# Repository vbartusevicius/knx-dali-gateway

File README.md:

# KNX–DALI Gateway

Open-source DIN-rail gateway between a wired **KNX TP** line and one **DALI / DALI-2** line: up to 64 control gear plus DALI-2 multi-master input devices, commissioned entirely through **ETS**. An optional integrated, isolated DALI bus supply runs from 20–32 V auxiliary DC (a 24 V PSU or the KNX white/yellow pair); the same input also powers the gateway core, with the KNX bus as a seamless fallback. The WiFi dashboard and MQTT are extras: lighting control and ETS provisioning never depend on them.

> [!NOTE]
> **Pre-hardware prototype.** Verified by native unit tests, a Docker KNX/DALI integration lab, KiCad DRC and isolation checks, JLCPCB footprint and pinout checks, and exact-solid CadQuery fit tests. No board has been powered on yet, and no KNX or DALI certification is claimed.

<p align="center">
  <a href="#downloads">Downloads</a> ·
  <a href="#screenshots">Screenshots</a> ·
  <a href="#hardware">Hardware</a> ·
  <a href="#building-one">Building one</a> ·
  <a href="#how-it-works">How it works</a> ·
  <a href="#development">Development</a>
</p>

---

## Downloads

| What | Where | Use |
| --- | --- | --- |
| **First install (USB)** | [`firmware-full-usb.bin`](https://github.com/vbartusevicius/knx-dali-gateway/releases/latest) | Bootloader, partition table and firmware in one image for an empty ESP32-C6. Connect the XIAO over USB-C and write it at `0x0`: `esptool.py --chip esp32c6 write_flash 0x0 firmware-full-usb.bin`. Clears all settings. |
| **Update** | [`firmware.bin`](https://github.com/vbartusevicius/knx-dali-gateway/releases/latest) | Drop it onto the **Firmware** tab of the web interface. Updates firmware and web UI together; settings are kept. |
| **ETS product database** | [`KnxDaliGateway.knxprod`](https://github.com/vbartusevicius/knx-dali-gateway/releases/latest) | Import into ETS 5.7 / 6: 64 lamp channels (DT6/DT7/DT8), 16 groups, broadcast, 8 DALI-2 input devices with up to 4 instances each (1,321 group objects). |
| **Hardware bundles** | [`knx-dali-gateway-hardware-v2.zip` / `v3.zip`](https://github.com/vbartusevicius/knx-dali-gateway/releases/latest) | Gerbers, JLCPCB BOM/CPL, STEP assemblies, printable STL/3MF case, `assembly_parts.csv`. |

---

## Screenshots

The web interface is built into the firmware and served by the ESP32-C6 itself (live WebSocket updates, no cloud):

<details>
<summary><b>More of the web interface</b>: lamp settings, groups and scenes, error log, bus monitor, settings</summary>

<br>

| Lamp settings | Groups & scenes |
| :---: | :---: |
|  |  |
| Device type, dimming curve, limits, fade, D4i or calculated power, ballast replacement | 16 scenes, 16 groups (G00–G15), group colour, membership written to the ballast |
| **Error log** | **Live DALI bus monitor** |
|  |  |
| Persistent NVS history with remedies | 8/16/24-bit frames and collisions: 1,024 rows on the device, 10,000 in the browser |
| **Settings** | |
|  | |
| WiFi, MQTT with Home Assistant auto-discovery, power model | |

- **Overview:** live level, DT8 colour (Tc, RGBW, xy), per-lamp power (native D4i Part 252 or calculated), lamp finder, fault codes; a second grid for DALI-2 buttons and sensors (IEC 62386-103 / 301–304).
- **Home Assistant:** one gateway device (total power and energy) plus every populated lamp with on/off, dimming, colour, power and fault entities.

</details>

<details>
<summary><b>Front-panel OLED pages</b>: V3 portrait 64×128, V2 landscape 128×64</summary>

<br>

The left button (SCROLL, plain bump) steps through the pages; holding it for 5 s starts the WiFi setup portal. The right button (RESET, bump with an X) reboots on a tap and toggles KNX programming mode when held for 5 s; both held for 10 s is a factory reset.

</details>

---

## Hardware

Two variants share the circuit blocks (`hardware/circuits/blocks/`), the XIAO ESP32-C6 pinout (`gateway/src/firmware/Board.hpp`) and the firmware:

| | **V3** (`v3`) | **V2** (`v2`) |
| --- | --- | --- |
| Width | 1 DIN (18 mm) | 2 DIN (36 mm) |
| Boards | 2: two-sided vertical `main`, front `ui` | 3: `main`, `interface`, `ui` |
| AUX core converter | TRACO TMR 2411 (2 W), on a tongue of `main` in the front protrusion | TRACO TRN 3-2411 (3 W), on the back of `main` |
| DALI terminal | WAGO 2086 push-in (SMD, hand-soldered), buttons beside the wire entries | MX126 screw |
| KNX / AUX | PST 1,0 pin strips (red/black, yellow/white plugs) | PST 1,0 KNX, MX126 screw AUX |
| Display | 0.96" 64×128 portrait SSD1312, solder flex tail | 0.96" 128×64 SSD1306 module, 4-pin header |
| Buttons | Omron B3U pressed through C-shaped spring tabs in the cover | same |
| Main ↔ UI link | 8-pin 0.5 mm FFC (Type B, 50 mm) | 10-pin JST-SH cable |
| Case | Side-opening clamshell, snap-fit | Two 2.5×10 screws, UI snaps |
| Release | [`hardware/releases/v3/`](hardware/releases/v3/README.md) | [`hardware/releases/v2/`](hardware/releases/v2/README.md) |

<details>
<summary><b>V3 renders</b>: assembly and boards</summary>

<br>

PCB artwork: [`main` top](hardware/releases/v3/main/renders/top.svg) · [bottom](hardware/releases/v3/main/renders/bottom.svg) · [`ui` top](hardware/releases/v3/ui/renders/top.svg) · [bottom](hardware/releases/v3/ui/renders/bottom.svg).
Fit drawings: [front](hardware/releases/v3/enclosure/fit_front.svg) · [side](hardware/releases/v3/enclosure/fit_side.svg).

</details>

<details>
<summary><b>V2 renders</b>: assembly and boards</summary>

<br>

PCB artwork: [`main` top](hardware/releases/v2/main/renders/top.svg) · [bottom](hardware/releases/v2/main/renders/bottom.svg) · [`interface` top](hardware/releases/v2/interface/renders/top.svg) · [bottom](hardware/releases/v2/interface/renders/bottom.svg) · [`ui` top](hardware/releases/v2/ui/renders/top.svg) · [bottom](hardware/releases/v2/ui/renders/bottom.svg).
Fit drawings: [front](hardware/releases/v2/enclosure/fit_front.svg) · [side](hardware/releases/v2/enclosure/fit_side.svg).

</details>

Pin table, LED chain and button ladder: [`hardware/docs/variants.md`](hardware/docs/variants.md). Pre-manufacturing reviews: [`review-2026-10-23.md`](hardware/docs/review-2026-10-23.md), [`review-2026-10-22.md`](hardware/docs/review-2026-10-22.md); rework for boards made from `59eea1f`: [`rework-rev-c.md`](hardware/docs/rework-rev-c.md).

---

## Building one

Each `hardware/releases/<variant>/` folder is a complete manufacturing package.

1. **PCBs with SMT assembly (JLCPCB).** Upload `panel/panel_gerbers.zip` (V3: 66.0 × 78.1 mm, 4 layers, 1.2 mm; V2: 98.5 × 76.6 mm, 4 layers, 1.6 mm) with **assembly on both sides**, `panel/panel_bom_jlc.csv` and `panel/panel_cpl_jlc.csv`. You order one PCB and one PCBA job and snap the boards apart. Per-board files are in `main/`, `ui/` (and `interface/` on V2). Compare `renders/top.svg` / `bottom.svg` with JLCPCB's placement preview.
   **Building it yourself:** `order_lcsc.csv` (LCSC BOM tool: map *LCSC Part Number* and *Quantity*) and `order_elsewhere.csv` (electronics LCSC does not sell, with Mouser / Digi-Key / TME numbers) cover every electronic part of one gateway; screws, foam and printed parts are only in `assembly_parts.csv`.
   **Other board houses** (Aisler, PCBWay, Eurocircuits, ...): every folder also has `<board>_odb.zip` (ODB++), Gerbers with drills and an IPC-D-356 netlist in `<board>_gerbers.zip`, and a generic `<board>_bom.csv` / `<board>_cpl.csv` with manufacturer part numbers and KiCad rotations.
2. **Hand-fitted parts.** `assembly_parts.csv` lists everything JLCPCB does not place (Kind `electronics`, `utility` or `printed`), with Mouser, Digi-Key and TME numbers:
   - the XIAO ESP32-C6 (pre-soldered) and its sockets;
   - the RECOM REC3-2415SRW/H2/A/CTRL DALI supply converter;
   - the TRACO AUX core converter;
   - Phoenix PST pin strips and plugs;
   - the OLED, the main-to-UI cable, and two jumper caps for `JP1`.
3. **Case.** Print `enclosure/base.stl` and one cover in PETG or ASA at 0.2 mm layers: `cover.stl`; V2 also has `cover_embossed.stl` (0.6 mm recessed legend). V3 has no front text: the button bumps tell the buttons apart.

<details>
<summary><b>V3 assembly order</b></summary>

1. Lay the OLED face down in the cover recess, fold its flex tail through the UI board's top notch and solder it to `J2`, put the 4 mm foam pad on the UI board, snap the UI board in.
2. Slide `main` into the base from the open left side, so the KNX/AUX pins pass into the right-side pockets and `J3` seats in the top opening.
3. Plug the FFC into `main J4` and `ui J1`, then close the cover over the left side and front until the four side snaps lock.

</details>

---

## How it works

- **KNX side:** an onsemi NCN5130 transceiver (TP1, 9-bit UART) charges a 470 µF store. An SCT2400 buck makes 5 V from it, with an undervoltage lockout above the NCN5130 reset level.
- **Core supply:** the AUX input feeds an isolated TRACO converter (SELV-AUX to SELV-KNX). A leaded priority path prefers it (TLV803 supervisor, 2N7002 and AO3401A switch) and a B5819W Schottky falls back to the KNX buck without a gap. A TI LM66100 keeps USB service power out of the core rail.
- **DALI supply:** the AUX input (PTC, TVS, reverse diode) feeds a RECOM REC3-2415SRW/H2/A/CTRL (24 V → 15 V, functional isolation), then a linear current limiter. The firmware can switch it off through an optocoupler on its `CTRL` pin, and jumper `JP1` disconnects it for an external DALI PSU.
- **DALI transceiver:** TX uses a MOSFET sink with bootstrap gate drive and a 275–350 mA fault clamp. RX uses a zener threshold with a constant-current detector. Both cross a 5.5 mm (reinforced, IEC 60664-1 230 V OVC III) milled barrier through TLP383 optocouplers.
- **Front panel:** the OLED (I2C), two buttons on one ADC ladder, and three WS2812B-MINI-V3J RGB LEDs with gull-wing legs (status, KNX, DALI) behind a 5 V level shifter. All passives are 0805 or larger except three 0603 bus caps next to the NCN5130 on V3; the NCN5130 (QFN-40) is the only leadless chip, as no leaded KNX transceiver exists.

---

## Development

| Folder | Contents |
| --- | --- |
| `gateway/` | ESP32-C6 firmware (C++17, ESP-IDF / PlatformIO) and native unit tests |
| `knxprod/` | ETS product database source and `.knxprod` builder |
| `simulation/` | DALI bus simulator and Docker KNX/DALI integration lab |
| `hardware/` | SKiDL circuits, KiCad layouts, part data, build scripts, release packages |
| `mechanical/` | CadQuery enclosures, fit drawings, front legends, 3D renders |

| Task | Command |
| --- | --- |
| Build, route, render, release and test both hardware variants | `python3 hardware/scripts/build.py` |
| One variant or step | `python3 hardware/scripts/build.py v3 --eda` (`--cad`, `--release`, `--test`) |
| Refresh the README images (after a release) | `docker compose --profile hardware run --rm -T cad "python3 mechanical/scripts/readme_images.py"` |
| Firmware tests and ESP32-C6 build (writes `firmware.bin` and `firmware-full-usb.bin`) | `pio test -d gateway -e native && pio run -d gateway -e dev_c6 -e release_c6` |
| Refresh the clangd compilation database | `pio run -d gateway -e dev_c6 -t compiledb` |
| Integration lab | `simulation/run-tests.sh` |
| ETS package | `ETS_CV_DIR=knxprod/ETS knxprod/scripts/package.sh` |
| Lint (Python, YAML, C++) | `docker compose --profile lint run --rm lint check .` |

Licences per folder: [`LICENSE.md`](LICENSE.md). Engineering rules and architecture notes: [`AGENTS.md`](AGENTS.md).

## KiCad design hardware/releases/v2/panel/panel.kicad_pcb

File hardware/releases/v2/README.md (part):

# KNX-DALI gateway hardware v2 (2 DIN, three boards)

**Revision C (2026-10-22).** Changes against rev B (`59eea1f`): AUX-powered core (TRACO TMR 1-2411 U9 on the back of main, hand-fitted, plus TI TPS2121 U10 priority mux with the KNX buck as fallback; U4 and C4 moved); XIAO LM66100 U7 (UI) CE on VOUT (no USB back-feed); DALI TX clamp 2R, gate divider 4k7/10k, RX pull-up 4k7 (interface), buck EN 100k (main); cover screw tab centred between the terminals and lips notched at the terminal bodies. Rev B boards and prints: follow [`hardware/docs/rework-rev-c.md`](../../docs/rework-rev-c.md).

**Hand-assembly revision (2026-11-11).** Every part is chosen for soldering with an iron:
- **Passives:** all 0805 or larger. The one exception is v3's three NCN5130 bus caps (C1 47 nF, C2 100 nF, C3 220 nF), which are 0603 so the chip's left side stays routable.
- **LEDs:** WS2812B-MINI-V3J with gull-wing legs (LCSC C22371519).
- **Crystal:** 2-pad 5032.
- **Core power path:** leaded parts (TLV803M U10, 2N7002 Q10, AO3401A Q9, B5819W D11) replace the VQFN TPS2121.
- **Still fine-pitch:** the NCN5130 (QFN-40; no leaded KNX transceiver exists: hot plate or hot air) and the LM66100 (SC-70-6, leaded).
- **Isolation:** DALI isolation is 5.5 mm (reinforced, IEC 60664-1 230 V OVC III PD2); SELV-AUX to SELV-KNX is 1 mm (functional).
- **Buttons:** left = SCROLL (plain bump), right = RESET (X bump).
- `<board>/<board>_assembly.pdf`: hand-soldering guide. One page per populated side (the bottom mirrored, as seen from below), each part's body, reference and value, a red dot on pin 1, a black corner on hand-fitted parts and one colour per value. Large parts are dashed under the small ones. A values page lists quantity, side and references.

Generated by `HARDWARE_VARIANT=v2 python3 hardware/scripts/release.py` from
`hardware/layout/v2/`, with the gates of every release: KiCad DRC 0 errors and 0
unrouted, every part orderable or hand-fit, every JLC part checked against
JLCPCB's part record, live stock and its EasyEDA footprint (pin for pin; the
placement file carries the fitted rotations and centres). CI
(`HARDWARE_VARIANT=v2`, `test_release_current.py`) fails as soon as the boards
no longer match this release.

| Board | Size | Layers | Position in the case | Folder |
|---|---|---|---|---|
| Main | 31.5 x 76.5 mm | 4 | flat in the base: KNX, 5 V, isolated DALI supply, all terminals | `main/` |
| Interface | 31.5 x 27.5 mm | 4 | plugged onto main (11 mm above it): isolated DALI TX/RX | `interface/` |
| UI | 31.5 x 40.5 mm | 4 | snapped into the cover: XIAO ESP32-C6, OLED, 2 buttons, 3 RGB LEDs | `ui/` |

The interface board has no case retention of its own: its two male headers
(J1 logic, J2 DALI, on its back) plug into main J6/J5 (8.5 mm sockets +
2.5 mm header plastic = 11.0 mm). DALI TX/RX reach it from the XIAO through
the main-to-UI cable (pins 7/8) and main J6. The only cable is that 10-pin
JST-SH jumper.

## Ordering at JLCPCB

1. Upload `<board>_gerbers.zip`: 4 layers, 1.6 mm, all three boards
   (standard JLC04161H-7628 stack-up; main has 0.2 mm thermal vias).
2. PCB Assembly, both sides: `<board>_bom_jlc.csv` + `<board>_cpl_jlc.csv`.
   Through-hole parts in the BOMs (main J5/J6 sockets and JP1, interface J1/J2
   headers on its back, terminals J2/J3) go to JLC's THT service.
3. `<board>_assembly_check.csv` lists JLCPCB footprint, rotation and stock for
   every part. Glance at the placement preview for the bottom-side parts
   (main: C3, L1, R1-R3; interface: C1, D1, D2, J1, J2, R4, R5, R7; UI: C5,
   C7, J1); their rotation follows JLCPCB's documented bottom convention.
   Pin 1 / polarity: optocouplers, transistors, the bridge's + corner, WS2812B-MINI-V3J
   corner marks, diode bands.

## Ordering elsewhere (Aisler, PCBWay, Eurocircuits, ...)

Each board folder and `panel/` also holds fab-independent files:

- `<board>_odb.zip`: ODB++ (copper, drills, outline, netlist, component
  placement). Aisler's preferred upload; PCBWay and Eurocircuits accept it.
- `<board>_gerbers.zip`: Gerber X2 per layer, Excellon drills (plated and
  non-plated) and `<board>.d356`, the IPC-D-356 netlist for the electrical test.
- `<board>_bom.csv`: every part with value, footprint, manufacturer part number
  (LCSC number for reference), SMD/THT, and whether the assembler or you fit it.
- `<board>_cpl.csv`: placement of the assembled parts in KiCad's coordinates
  and rotations (the `_jlc` files use JLCPCB's rotations and are for JLCPCB only).

Order the stack-up, thickness and finish given above; check the assembler's
placement preview for the bottom-side and rotated parts as for JLCPCB.

## Ordering the parts yourself

For one complete gateway (all boards and hand-fit parts), in this folder:

- `order_lcsc.csv`: LCSC BOM tool (lcsc.com → BOM Tool, map **LCSC Part Number** and
  **Quantity**). Every board part plus the hand-fit parts LCSC sells; one line per LCSC number,
  designators as `board:ref`. Multiply the quantities for more gateways; LCSC rounds up to each
  part's minimum order.
- `order_elsewhere.csv`: the electronics LCSC does not sell (XIAO, REC3, converters, Phoenix pin
  strips and plugs, OLED, cable), with every Mouser / Digi-Key / TME number. A cell may list
  alternatives, e.g. `713-102010636 (or 713-113991254)`; buy one of them.
- `assembly_parts.csv`: everything not placed by the assembler, with a **Kind** column:
  `electronics` (the hand-fit parts above), `utility` (screws, foam pad, lead trimming) and
  `printed` (case parts). Utility and printed items are not in the order files; get them locally.

Not needed when JLCPCB assembles the boards: then order only the hand-fit lines.

## Front legend (optional print)

Three flat faces carry the legend (3 mm letters, 0.6 mm deep): bottom shoulder (KNX only: the keyed plug fits one way round), front (SCROLL,
RESET; the LEDs are unmarked: STATUS, KNX, DALI from left to right) and top shoulder (- + "20-32V" and DA DA "BUS", enclosed by one bracket
with DALI in its bar: this input feeds only the internal DALI bus supply,
not the gateway). 20-32 V keeps margin to the REC3 start-up (18 V max plus
the SS16 reverse-polarity drop) and to the 33 V PTC/TVS limit; a 24 V
supply or the MDT STC-1280.01 30 V output are both inside.

- `enclosure/cover_embossed.stl` (also `.step`): the cover with the legend
  recessed 0.6 mm into its faces, for single-colour printing.

## Hand-fitted parts (`<board>_hand_fit.csv`)

- Main J1: Phoenix 1574200 KNX pin strip. The red/black KNX plug goes in from
  the front into a cover pocket sized for the WAGO 243-211 (11.5 x 10.2 x 10.2 mm,
  measured, 0.3 mm clearance all round, a slot for the butterfly key on the
  right wall). It sits directly on the strip, where its sockets meet the pins;
  its wire entries face down, about 2.8 mm inside the open bottom of the
  pocket, and its top stays 1.3 mm behind the bottom shoulder face.
- Main U3: RECOM REC3-2415SRW/H2/A/CTRL (DIP-24, A pinning with pin 1 CTRL; clip unused pins 3 and 11 flush).
- Main C4: 470 uF 35 V, D10 x 16 (SamYoung KMG35V470M10*16 LO, LCSC C165500), **lying down
  on the back**: bend both leads 90 deg 3 mm from the body, insert from the
  back so the body axis is 7 mm below the board (2 mm air gap) and runs
  towards the KNX end, solder on the front, trim. It rests in two cradles in
  the base; the leads do not carry it. Minus stripe to pad 2 (round pad).
- UI U2: Seeed XIAO ESP32C6 **Pre-Soldered (SKU 102010636)**, detachable in
  two 1x7 8.5 mm female headers soldered to the back of the UI board (the bare
  113991254 ships without pin headers); module 11 mm above the board. Silkscreen marks
  USB, D0 and 5V. For USB flashing unsnap the UI board (it stays on its cable)
  or pull the XIAO out; with the board in the cover the protrusion wall
  blocks a straight USB-C plug.
- UI J2: Winstar **WEA012864DWPP3N00003** (WEA012864D-03, 0.96" 128x64
  SSD1306 I2C, white; `...DLPP...` yellow, `...DBPP...` sky blue), pin order
  VCC, GND, SCL, SDA. Do not use generic modules: their size, glass position
  and pin order differ. Drawing: WEA012864D-03 datasheet p.3.

Off-board parts are in `assembly_parts.csv` (10-pin JST-SH 1:1 cable, KNX bus
plug Phoenix PTS 0,5/2-PH-5,75 BKRD, XIAO sockets, two JP1 jumper caps, two
2.5 x 10 thread-forming screws, the two printed parts).

## Assembly

1. Main board: C4 lying down as above, both JP1 caps if the gateway should
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
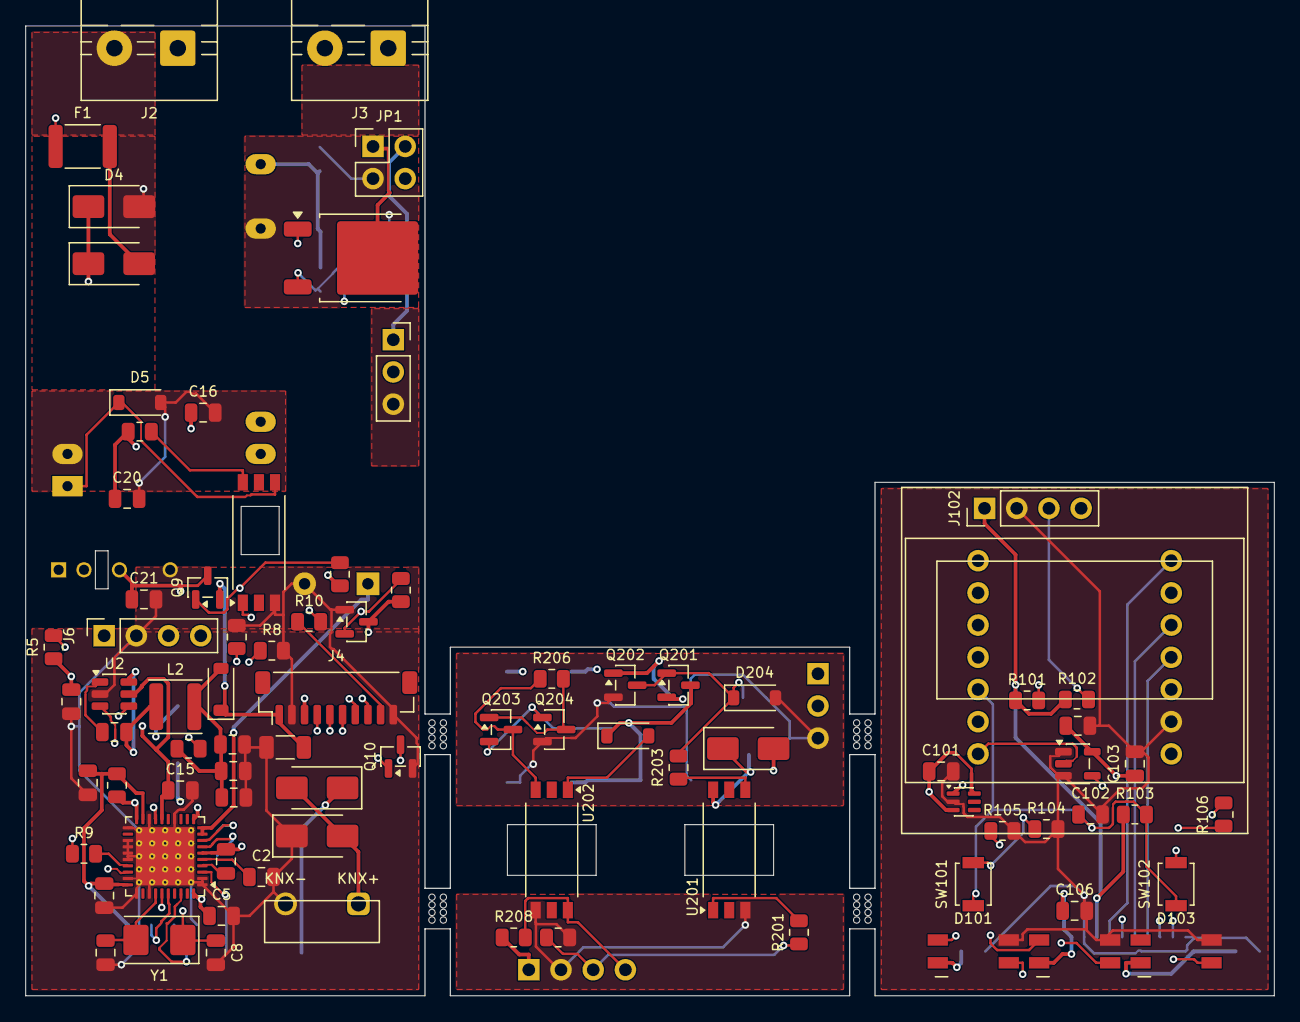
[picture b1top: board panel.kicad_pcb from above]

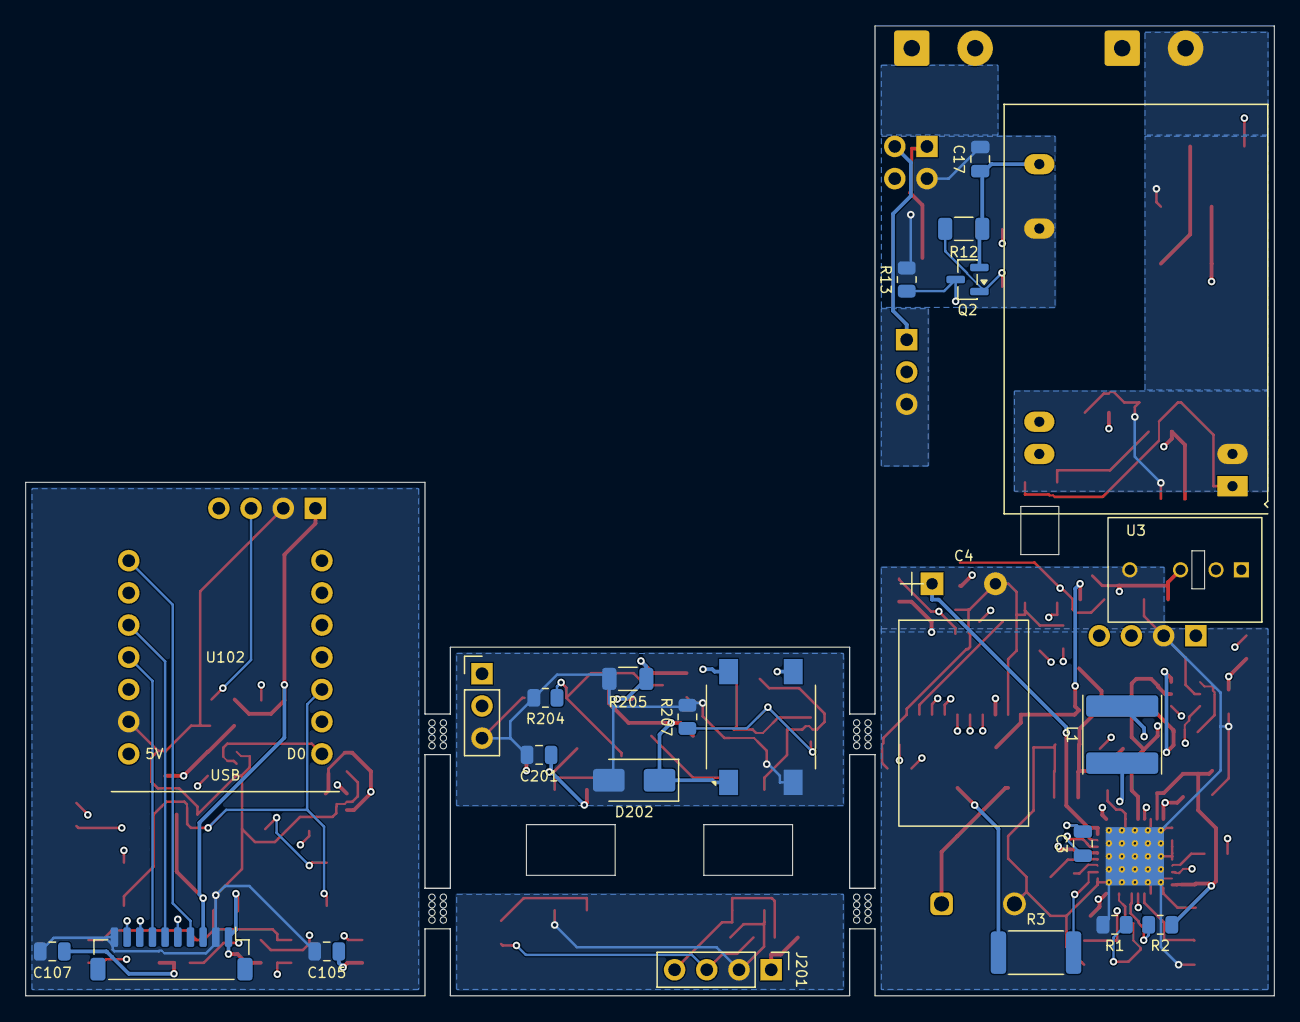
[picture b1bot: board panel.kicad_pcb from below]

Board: 4 copper layers, 98.5 x 76.5 mm, 139 parts (24 on the bottom side), 83 nets.

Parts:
C1: 47n 50V; C_0805_2012Metric
C2, C5, C6, C10, C14, C102, C104, C105, C106, C107: 100n 50V; C_0805_2012Metric
C3: 220n 50V; C_0805_2012Metric
C4: 470u 35V; CP_Radial_D10.0mm_P5.00mm_Horizontal_Bent
C7, C12, C13: 22u 25V; C_0805_2012Metric
C8, C9: 33p C0G 50V; C_0805_2012Metric
C11, C16, C20: 10u 50V; C_0805_2012Metric
C15, C103, C201: 1u 50V; C_0805_2012Metric
C17, C21, C101: 10u 25V; C_0805_2012Metric
C23: 100u 6.3V; C_1206_3216Metric
D1: SMAJ40CA; D_SMA
D2, D3, D203: SS16; D_SMA
D4: SMAJ33A; D_SMA
D5, D205: 5V6; D_SOD-123
D11: B5819W; D_SOD-123
D101: RGB STATUS; LED_WS2812B-MINI-V3J_3.5x3.5mm
D102: RGB KNX; LED_WS2812B-MINI-V3J_3.5x3.5mm
D103: RGB DALI; LED_WS2812B-MINI-V3J_3.5x3.5mm
D201: DF06S; Diode_Bridge_Vishay_DFS
D202: SMAJ24A; D_SMA
D204: 12V; D_SOD-123
F1: 1.1A; Fuse_1812_4532Metric
J1: KNX bus terminal pins; Phoenix_PST_1,0-2-5,75_R32_1x02_P5.75mm
J2: AUX; TerminalBlock_MaiXu_MX126-5.0-02P_1x02_P5.00mm
J3: DALI; TerminalBlock_MaiXu_MX126-5.0-02P_1x02_P5.00mm
J4, J101: Controller cable; JST_SH_BM10B-SRSS-TB_1x10-1MP_P1.00mm_Vertical
J5: Interface DALI; PinSocket_1x03_P2.54mm_Vertical
J6: Interface logic; PinSocket_1x04_P2.54mm_Vertical
J102: OLED; PinHeader_1x04_P2.54mm_Vertical
J201: Main logic; PinHeader_1x04_P2.54mm_Vertical
J202: Main DALI; PinHeader_1x03_P2.54mm_Vertical
JP1: DALI supply; PinHeader_2x02_P2.54mm_Vertical
L1: 220uH; L_Sunlord_SWPA6045S
L2: 4.7uH; L_APV_ANR4012
MB1, MB2, MB3, MB4, MB5, MB6, MB7, MB8, MB9, MB10, MB11, MB12, MB13, MB14, MB15, MB16, MB17, MB18, MB19, MB20, MB21, MB22, MB23, MB24, MB25, MB26, MB27, MB28, MB29, MB30, MB31, MB32: DNP
Q1: MJD45H11; TO-252-2
Q2: BC857; SOT-23
Q9: AO3401A; SOT-23
Q10: 2N7002; SOT-23
Q201: IRLML0060; SOT-23
Q202, Q203, Q204: BC847; SOT-23
R1, R6, R8: 10k 1%; R_0805_2012Metric
R2, R11, R25, R103, R104, R202, R204: 10k; R_0805_2012Metric
R3: 27R; R_2512_6332Metric
R4: 1R; R_0805_2012Metric
R5: 100k 1%; R_0805_2012Metric
R7: 51k 1%; R_0805_2012Metric
R9: 1k; R_0805_2012Metric
R10, R106, R201: 330R; R_0805_2012Metric
R12: 3R3; R_1206_3216Metric
R13, R101, R102, R203, R208: 4k7; R_0805_2012Metric
R24, R206: 100k; R_0805_2012Metric
R105: 20k; R_0805_2012Metric
R205: 2R; R_1206_3216Metric
R207: 680R; R_0805_2012Metric
SW101: SCROLL; SW_SPST_B3U-1000P
SW102: RESET; SW_SPST_B3U-1000P
U1: NCN5130MNTWG; QFN-40-1EP_6x6mm_P0.5mm_EP4.6x4.6mm_ThermalVias
U2: SCT2400TVBR; TSOT-23-6
U3: REC3-2415SRW/H2/A/CTRL 24V->15V 3W iso; Converter_DCDC_RECOM_REM3_DIP24_CTRL
U4: TLP383; SO-6L_10x3.84mm_P1.27mm
U9: TRN 3-2411 24V->5V 3W iso; Converter_DCDC_TRACO_TRN3_SIP5
U10: TLV803M supervisor; SOT-23
U101: LM66100; SOT-363_SC-70-6
U102: XIAO ESP32C6; XIAO_ESP32C6_Header
U103: 74AHCT1G125; SOT-23-5
U201, U202: TLP383(D4BLLTL,E; SO-6L_10x3.84mm_P1.27mm
Y1: 16MHz; Crystal_SMD_5032-2Pin_5.0x3.2mm

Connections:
+3V3: J4.3, J6.1
+3V3_TRX: C5.1, C6.1, C7.1, R2.1, R4.2, U1.11, U1.19, U1.30, U1.40
+5V: C23.1, D11.1, J4.1, Q9.2, R25.1
+5V_AUX: C21.1, Q9.3, R24.1, U9.3, U10.3
+5V_BUCK: C12.1, C13.1, C14.1, D11.2, L2.2, R7.1
AUX_FUSED: D3.2, F1.2
AUX_P: C16.1, C20.1, D3.1, D4.1, R11.1, U3.22, U3.23, U9.2
CAV: C2.1, U1.5
CCP: C1.2, U1.4
CEQ1: C3.1, U1.7
CEQ2: C3.2, U1.8
CORE_AUX_GOOD: Q10.1, R24.2, U10.2
CORE_PFET_G: Q9.1, Q10.3, R25.2
DA1: J3.1, J5.1, JP1.2
DA2: J3.2, J5.2, JP1.4
DALI_ISO15V: C17.1, Q2.2, R12.1, U3.14
DALI_RX: J4.8, J6.4
DALI_SUPPLY_OFF: J4.9, R10.1
DALI_SUPPLY_SW: JP1.1, Q1.2
DALI_TX: J4.7, J6.3
FANIN: R1.1, U1.38
GND: C2.2, C4.2, C5.2, C6.2, C7.2, C8.2, C9.2, C11.2, C12.2, C13.2, C14.2, C15.2, C21.2, C23.2, D1.1, J1.2, J4.2, J4.10, J6.2, Q10.2, R1.2, R6.2, R8.2, U1.1, U1.2, U1.14, U1.18, U1.21, U1.23, U1.24, U1.25, U1.26, U1.29, U1.31, U1.33, U1.41, U2.2, U4.3, U9.5, U10.1
GNDA: C16.2, C20.2, D4.2, D5.2, J2.2, U3.2, U9.1
GNDD: C17.2, J5.3, JP1.3, R13.2, U3.16
INTERFACE_+3V3: J201.1, R208.1
INTERFACE_DA1: D201.3, J202.1
INTERFACE_DA2: D201.4, J202.2
INTERFACE_DALI_BOOT: C201.1, D203.1, U201.6
INTERFACE_DALI_GATE: D204.1, Q201.1, Q202.3, R203.2, R204.1
INTERFACE_DALI_GATE_SW: R203.1, U201.4
INTERFACE_DALI_RX: J201.4, R208.2, U202.6
INTERFACE_DALI_SENSE: Q201.2, Q202.1, R205.1
INTERFACE_DALI_TX: J201.3, R201.1, R202.1
INTERFACE_DA_P: D201.1, D202.1, D203.2, D205.1, Q201.3
INTERFACE_GND: J201.2, R202.2, U201.3, U202.4
INTERFACE_GNDD: C201.2, D201.2, D202.2, D204.2, J202.3, Q202.2, Q204.2, R204.2, R205.2, R207.2
INTERFACE_N$1: R201.2, U201.1
INTERFACE_N$2: D205.2, U202.1
INTERFACE_N$3: Q203.2, Q204.1, R207.1
INTERFACE_N$4: Q203.1, Q204.3, R206.2
INTERFACE_RX_LIM_IN: Q203.3, R206.1, U202.3
KNX_P: D1.2, D2.2, J1.1
KNX_P_PROT: C1.1, D2.1, R3.1, U1.6
KNX_RXD: J4.5, R9.1
KNX_TXD: J4.4, U1.28
unnamed: R5.2, R6.1, U2.4
unnamed: C10.1, U2.1
unnamed: R7.2, R8.1, U2.3
unnamed: R9.2, U1.27
unnamed: F1.1, J2.1
unnamed: R10.2, U4.1
unnamed: R11.2, U4.6
unnamed: D5.1, U3.1, U4.4
unnamed: Q1.3, Q2.1, R12.2
unnamed: Q1.1, Q2.3, R13.1
NCN_SAVEB: J4.6, R2.2, U1.36
SW: C10.2, L2.1, U2.6
TX0: R3.2, U1.3
UI_+3V3: J101.3, J102.1, R101.1, R102.1, R103.1, U102.12
UI_+5V: C103.1, C104.1, C105.1, C106.1, C107.1, D101.1, D102.1, D103.1, J101.1, U101.1, U103.5
UI_+5V_XIAO: C101.1, U101.3, U101.6, U102.14
UI_BTN_LADDER: C102.1, R103.2, SW101.1, SW102.1, U102.3
UI_DALI_RX: J101.8, U102.9
UI_DALI_SUPPLY_OFF: J101.9, U102.2
UI_DALI_TX: J101.7, U102.11
UI_GND: C101.2, C102.2, C103.2, C104.2, C105.2, C106.2, C107.2, D101.3, D102.3, D103.3, J101.2, J101.10, J102.2, R104.2, R105.2, U101.2, U102.13, U103.1, U103.3
UI_I2C_SCL: J102.3, R102.2, U102.6
UI_I2C_SDA: J102.4, R101.2, U102.5
UI_KNX_RXD: J101.5, U102.7
UI_KNX_TXD: J101.4, U102.8
UI_LED_CHAIN1: D101.2, D102.4
UI_LED_CHAIN2: D102.2, D103.4
UI_LED_DATA: U102.1, U103.2
UI_N$1: R104.1, SW101.2
UI_N$2: R105.1, SW102.2
UI_N$3: R106.1, U103.4
UI_N$4: D101.4, R106.2
UI_NCN_SAVEB: J101.6, U102.10
VDD1M: L1.2, R4.1, U1.20
VFILT: C4.1, C11.1, C15.1, R5.1, U1.9, U1.10, U1.16, U2.5
VSW1: L1.1, U1.17
XTAL1: C8.1, U1.35, Y1.1
XTAL2: C9.1, U1.34, Y1.2

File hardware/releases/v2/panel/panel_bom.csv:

Designator,Quantity,Value,Footprint,Manufacturer Part Number,LCSC Part #,Mount,Fitted by
F1,1,1.1A,Fuse_1812_4532Metric,1812L110/33MR,C142747,SMD,assembler
"R206,R24",2,100k,R_0805_2012Metric,0805W8F1003T5E,C149504,SMD,assembler
R5,1,100k 1%,R_0805_2012Metric,0805W8F1003T5E,C149504,SMD,assembler
"C10,C102,C104,C105,C106,C107,C14,C2,C5,C6",10,100n 50V,C_0805_2012Metric,CC0805KRX7R9BB104,C49678,SMD,assembler
C23,1,100u 6.3V,C_1206_3216Metric,CL31A107MQHNNNE,C15008,SMD,assembler
"R103,R104,R11,R2,R202,R204,R25",7,10k,R_0805_2012Metric,0805W8F1002T5E,C17414,SMD,assembler
"R1,R6,R8",3,10k 1%,R_0805_2012Metric,0805W8F1002T5E,C17414,SMD,assembler
"C101,C17,C21",3,10u 25V,C_0805_2012Metric,CL21A106KAYNNNE,C15850,SMD,assembler
"C11,C16,C20",3,10u 50V,C_0805_2012Metric,GRM21BR61H106KE43L,C440198,SMD,assembler
D204,1,12V,D_SOD-123,MMSZ12T1G,C72599,SMD,assembler
Y1,1,16MHz,Crystal_SMD_5032-2Pin_5.0x3.2mm,TAXM16M2QLFCDT1T,C122519,SMD,assembler
R4,1,1R,R_0805_2012Metric,0805W8F100KT5E,C25271,SMD,assembler
R9,1,1k,R_0805_2012Metric,0805W8F1001T5E,C17513,SMD,assembler
"C103,C15,C201",3,1u 50V,C_0805_2012Metric,CL21B105KBFNNNE,C28323,SMD,assembler
R105,1,20k,R_0805_2012Metric,0805W8F2002T5E,C4328,SMD,assembler
C3,1,220n 50V,C_0805_2012Metric,CL21B224KBFNNNE,C5378,SMD,assembler
L1,1,220uH,L_Sunlord_SWPA6045S,SWPA6045S221MT,C91047,SMD,assembler
"C12,C13,C7",3,22u 25V,C_0805_2012Metric,CL21A226MAQNNNE,C45783,SMD,assembler
R3,1,27R,R_2512_6332Metric,25121WJ0270T4E,C25478,SMD,assembler
Q10,1,2N7002,SOT-23,2N7002,C8545,SMD,assembler
R205,1,2R,R_1206_3216Metric,1206W4F200KT5E,C17942,SMD,assembler
"R10,R106,R201",3,330R,R_0805_2012Metric,0805W8F3300T5E,C17630,SMD,assembler
"C8,C9",2,33p C0G 50V,C_0805_2012Metric,0805CG330J500NT,C157687,SMD,assembler
R12,1,3R3,R_1206_3216Metric,1206W4F330KT5E,C17945,SMD,assembler
L2,1,4.7uH,L_APV_ANR4012,SMNR4012-4R7MT,C135248,SMD,assembler
C1,1,47n 50V,C_0805_2012Metric,CC0805KRX7R9BB473,C107154,SMD,assembler
"R101,R102,R13,R203,R208",5,4k7,R_0805_2012Metric,0805W8F4701T5E,C17673,SMD,assembler
R7,1,51k 1%,R_0805_2012Metric,0805W8F5102T5E,C17737,SMD,assembler
"D205,D5",2,5V6,D_SOD-123,MMSZ5V6T1G,C236111,SMD,assembler
R207,1,680R,R_0805_2012Metric,0805W8F6800T5E,C17798,SMD,assembler
U103,1,74AHCT1G125,SOT-23-5,SN74AHCT1G125DBVR,C7484,SMD,assembler
Q9,1,AO3401A,SOT-23,AO3401A,C15127,SMD,assembler
J2,1,AUX,TerminalBlock_MaiXu_MX126-5.0-02P_1x02_P5.00mm,MX126-5.0-02P-GN01-Cu-S-A,C5188434,THT,assembler
D11,1,B5819W,D_SOD-123,B5819W SL,C8598,SMD,assembler
"Q202,Q203,Q204",3,BC847,SOT-23,BC847B,C57668,SMD,assembler
Q2,1,BC857,SOT-23,BC857C,C181147,SMD,assembler
"J101,J4",2,Controller cable,JST_SH_BM10B-SRSS-TB_1x10-1MP_P1.00mm_Vertical,BM10B-SRSS-TB(LF)(SN),C160396,SMD,assembler
J3,1,DALI,TerminalBlock_MaiXu_MX126-5.0-02P_1x02_P5.00mm,MX126-5.0-02P-GN01-Cu-S-A,C5188434,THT,assembler
JP1,1,DALI supply,PinHeader_2x02_P2.54mm_Vertical,2.54-2*2PPin,C66690,THT,assembler
D201,1,DF06S,Diode_Bridge_Vishay_DFS,DF06S-T,C460867,SMD,assembler
Q201,1,IRLML0060,SOT-23,IRLML0060TRPBF,C67274,SMD,assembler
J5,1,Interface DALI,PinSocket_1x03_P2.54mm_Vertical,KH-2.54FH-1X3P-H8.5,C2932670,THT,assembler
J6,1,Interface logic,PinSocket_1x04_P2.54mm_Vertical,KH-2.54FH-1X4P-H8.5,C2905415,THT,assembler
U101,1,LM66100,SOT-363_SC-70-6,LM66100DCKR,C2869734,SMD,assembler
Q1,1,MJD45H11,TO-252-2,MJD45H11,C48580717,SMD,assembler
J202,1,Main DALI,PinHeader_1x03_P2.54mm_Vertical,2.54-1*3P,C49257,THT,assembler
J201,1,Main logic,PinHeader_1x04_P2.54mm_Vertical,KH-2.54PH180-1X4P-L11.5,C2905435,THT,assembler
U1,1,NCN5130MNTWG,QFN-40-1EP_6x6mm_P0.5mm_EP4.6x4.6mm_ThermalVias,NCN5130MNTWG,C513000,SMD,assembler
SW102,1,RESET,SW_SPST_B3U-1000P,B3U-1000P,C231329,SMD,assembler
D103,1,RGB DALI,LED_WS2812B-MINI-V3J_3.5x3.5mm,WS2812B-MINI-V3J,C22371519,SMD,assembler
D102,1,RGB KNX,LED_WS2812B-MINI-V3J_3.5x3.5mm,WS2812B-MINI-V3J,C22371519,SMD,assembler
D101,1,RGB STATUS,LED_WS2812B-MINI-V3J_3.5x3.5mm,WS2812B-MINI-V3J,C22371519,SMD,assembler
SW101,1,SCROLL,SW_SPST_B3U-1000P,B3U-1000P,C231329,SMD,assembler
U2,1,SCT2400TVBR,TSOT-23-6,SCT2400TVBR,C2693819,SMD,assembler
D202,1,SMAJ24A,D_SMA,SMAJ24A,C148222,SMD,assembler
D4,1,SMAJ33A,D_SMA,SMAJ33A,C113966,SMD,assembler
D1,1,SMAJ40CA,D_SMA,SMAJ40CA,C113970,SMD,assembler
"D2,D203,D3",3,SS16,D_SMA,SS16,C2481,SMD,assembler
U4,1,TLP383,SO-6L_10x3.84mm_P1.27mm,"TLP383(D4BLLTL,E",C3002263,SMD,assembler
"U201,U202",2,"TLP383(D4BLLTL,E",SO-6L_10x3.84mm_P1.27mm,"TLP383(D4BLLTL,E",C3002263,SMD,assembler
U10,1,TLV803M supervisor,SOT-23,TLV803MDBZR-TP,C52817175,SMD,assembler
C4,1,470u 35V,CP_Radial_D10.0mm_P5.00mm_Horizontal_Bent,KMG35V470M10*16 LO,C165500,THT,hand-fit (not assembled)
J1,1,KNX bus terminal pins,"Phoenix_PST_1,0-2-5,75_R32_1x02_P5.75mm",1574200,,THT,hand-fit (not assembled)
J102,1,OLED,PinHeader_1x04_P2.54mm_Vertical,WEA012864DWPP3N00003,,THT,hand-fit (not assembled)
U3,1,REC3-2415SRW/H2/A/CTRL 24V->15V 3W iso,Converter_DCDC_RECOM_REM3_DIP24_CTRL,REC3-2415SRW/H2/A/CTRL,,THT,hand-fit (not assembled)
U9,1,TRN 3-2411 24V->5V 3W iso,Converter_DCDC_TRACO_TRN3_SIP5,TRN 3-2411,,THT,hand-fit (not assembled)
U102,1,XIAO ESP32C6,XIAO_ESP32C6_Header,102010636,,THT,hand-fit (not assembled)

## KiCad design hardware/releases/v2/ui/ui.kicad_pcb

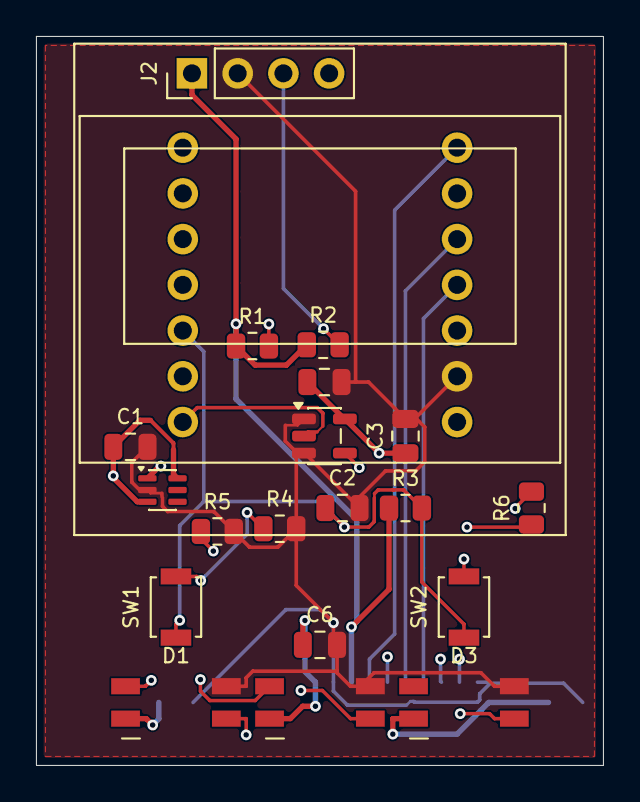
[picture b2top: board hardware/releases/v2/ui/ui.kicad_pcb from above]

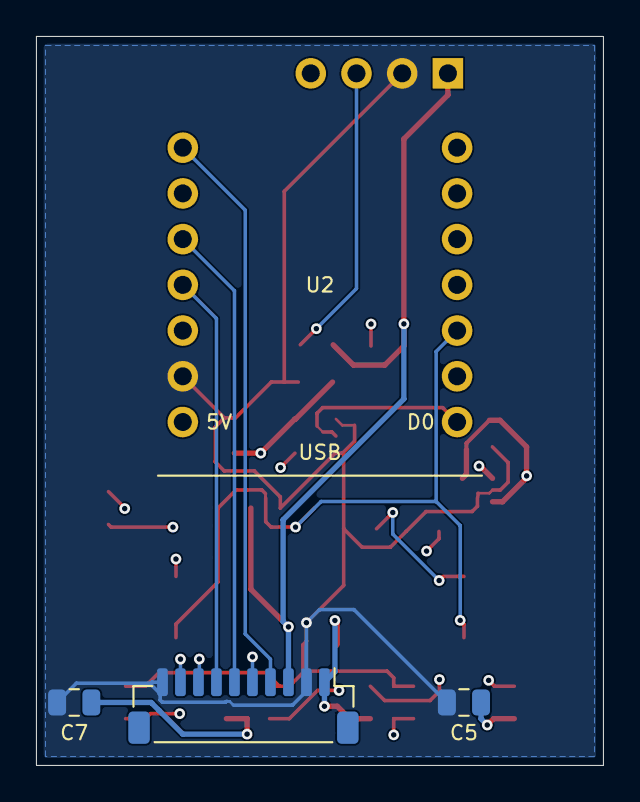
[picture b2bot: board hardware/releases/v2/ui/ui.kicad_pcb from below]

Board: 4 copper layers, 31.5 x 40.5 mm, 23 parts (4 on the bottom side), 20 nets.

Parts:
C1: 10u 25V; C_0805_2012Metric
C2, C4, C5, C6, C7: 100n 50V; C_0805_2012Metric
C3: 1u 50V; C_0805_2012Metric
D1: RGB STATUS; LED_WS2812B-MINI-V3J_3.5x3.5mm
D2: RGB KNX; LED_WS2812B-MINI-V3J_3.5x3.5mm
D3: RGB DALI; LED_WS2812B-MINI-V3J_3.5x3.5mm
J1: Controller cable; JST_SH_BM10B-SRSS-TB_1x10-1MP_P1.00mm_Vertical
J2: OLED; PinHeader_1x04_P2.54mm_Vertical
R1, R2: 4k7; R_0805_2012Metric
R3, R4: 10k; R_0805_2012Metric
R5: 20k; R_0805_2012Metric
R6: 330R; R_0805_2012Metric
SW1: SCROLL; SW_SPST_B3U-1000P
SW2: RESET; SW_SPST_B3U-1000P
U1: LM66100; SOT-363_SC-70-6
U2: XIAO ESP32C6; XIAO_ESP32C6_Header
U3: 74AHCT1G125; SOT-23-5

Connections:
+3V3: J1.3, J2.1, R1.1, R2.1, R3.1, U2.12
+5V: C3.1, C4.1, C5.1, C6.1, C7.1, D1.1, D2.1, D3.1, J1.1, U1.1, U3.5
+5V_XIAO: C1.1, U1.3, U1.6, U2.14
BTN_LADDER: C2.1, R3.2, SW1.1, SW2.1, U2.3
DALI_RX: J1.8, U2.9
DALI_SUPPLY_OFF: J1.9, U2.2
DALI_TX: J1.7, U2.11
GND: C1.2, C2.2, C3.2, C4.2, C5.2, C6.2, C7.2, D1.3, D2.3, D3.3, J1.2, J1.10, J2.2, R4.2, R5.2, U1.2, U2.13, U3.1, U3.3
I2C_SCL: J2.3, R2.2, U2.6
I2C_SDA: J2.4, R1.2, U2.5
KNX_RXD: J1.5, U2.7
KNX_TXD: J1.4, U2.8
LED_CHAIN1: D1.2, D2.4
LED_CHAIN2: D2.2, D3.4
LED_DATA: U2.1, U3.2
unnamed: R4.1, SW1.2
unnamed: R5.1, SW2.2
unnamed: R6.1, U3.4
unnamed: D1.4, R6.2
NCN_SAVEB: J1.6, U2.10

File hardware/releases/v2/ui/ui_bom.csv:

Designator,Quantity,Value,Footprint,Manufacturer Part Number,LCSC Part #,Mount,Fitted by
"C2,C4,C5,C6,C7",5,100n 50V,C_0805_2012Metric,CC0805KRX7R9BB104,C49678,SMD,assembler
"R3,R4",2,10k,R_0805_2012Metric,0805W8F1002T5E,C17414,SMD,assembler
C1,1,10u 25V,C_0805_2012Metric,CL21A106KAYNNNE,C15850,SMD,assembler
C3,1,1u 50V,C_0805_2012Metric,CL21B105KBFNNNE,C28323,SMD,assembler
R5,1,20k,R_0805_2012Metric,0805W8F2002T5E,C4328,SMD,assembler
R6,1,330R,R_0805_2012Metric,0805W8F3300T5E,C17630,SMD,assembler
"R1,R2",2,4k7,R_0805_2012Metric,0805W8F4701T5E,C17673,SMD,assembler
U3,1,74AHCT1G125,SOT-23-5,SN74AHCT1G125DBVR,C7484,SMD,assembler
J1,1,Controller cable,JST_SH_BM10B-SRSS-TB_1x10-1MP_P1.00mm_Vertical,BM10B-SRSS-TB(LF)(SN),C160396,SMD,assembler
U1,1,LM66100,SOT-363_SC-70-6,LM66100DCKR,C2869734,SMD,assembler
SW2,1,RESET,SW_SPST_B3U-1000P,B3U-1000P,C231329,SMD,assembler
D3,1,RGB DALI,LED_WS2812B-MINI-V3J_3.5x3.5mm,WS2812B-MINI-V3J,C22371519,SMD,assembler
D2,1,RGB KNX,LED_WS2812B-MINI-V3J_3.5x3.5mm,WS2812B-MINI-V3J,C22371519,SMD,assembler
D1,1,RGB STATUS,LED_WS2812B-MINI-V3J_3.5x3.5mm,WS2812B-MINI-V3J,C22371519,SMD,assembler
SW1,1,SCROLL,SW_SPST_B3U-1000P,B3U-1000P,C231329,SMD,assembler
J2,1,OLED,PinHeader_1x04_P2.54mm_Vertical,WEA012864DWPP3N00003,,THT,hand-fit (not assembled)
U2,1,XIAO ESP32C6,XIAO_ESP32C6_Header,102010636,,THT,hand-fit (not assembled)

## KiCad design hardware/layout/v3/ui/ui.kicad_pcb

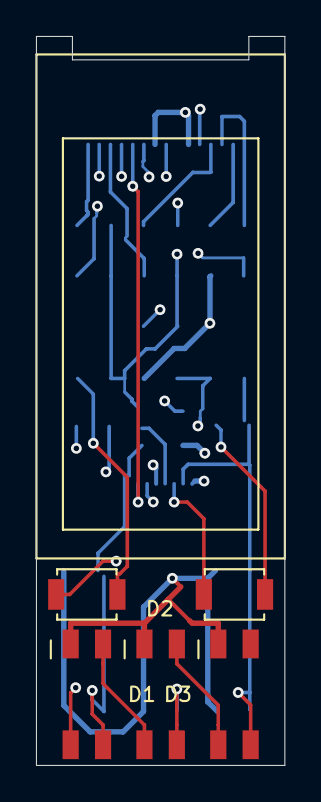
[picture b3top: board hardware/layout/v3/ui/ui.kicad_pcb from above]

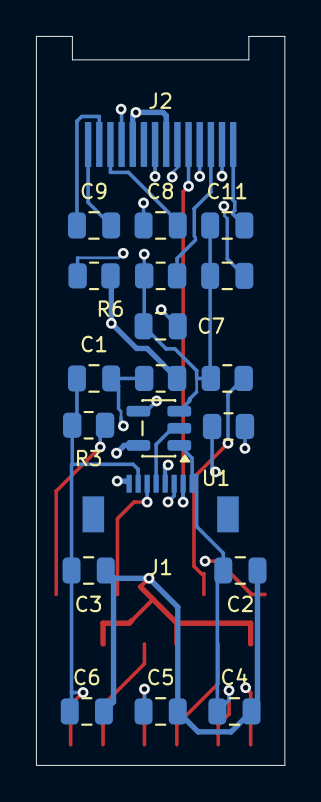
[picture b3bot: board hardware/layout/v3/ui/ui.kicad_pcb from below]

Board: 4 copper layers, 13.8 x 40.5 mm, 25 parts (20 on the bottom side), 21 nets.

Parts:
C1, C3, C4, C5, C6, C7: 100n 50V; C_0805_2012Metric
C2, C8, C9, C10, C11: 1u 50V; C_0805_2012Metric
D1: RGB STATUS; LED_WS2812B-MINI-V3J_3.5x3.5mm
D2: RGB KNX; LED_WS2812B-MINI-V3J_3.5x3.5mm
D3: RGB DALI; LED_WS2812B-MINI-V3J_3.5x3.5mm
J1: Carrier; FPC_Kinghelm_KH-FPC0.5-H1.2SMT-8P
J2: OLED; OLED_FPC_14P_P0.62mm_Hotbar
R1, R2, R5: 10k; R_0805_2012Metric
R3: 20k; R_0805_2012Metric
R4: 330R; R_0805_2012Metric
R6: 390k; R_0805_2012Metric
SW1: SCROLL; SW_SPST_B3U-1000P
SW2: RESET; SW_SPST_B3U-1000P
U1: 74AHCT1G125; SOT-23-5

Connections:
+3V3: J1.1, J2.5, J2.8, R1.1, R5.1
+5V: C2.1, C3.1, C4.1, C5.1, C6.1, D1.1, D2.1, D3.1, J1.5, U1.5
BTN_LADDER: C1.1, J1.3, R1.2, SW1.1, SW2.1
GND: C1.2, C2.2, C3.2, C4.2, C5.2, C6.2, C7.2, C10.2, C11.2, D1.3, D2.3, D3.3, J1.2, J1.8, J2.7, R2.2, R3.2, R6.2, U1.1, U1.3
I2C_SCL: J1.7, J2.10
I2C_SDA: J1.6, J2.11
LED_CHAIN1: D1.2, D2.4
LED_CHAIN2: D2.2, D3.4
LED_DATA: J1.4, U1.2
unnamed: R2.1, SW1.2
unnamed: R3.1, SW2.2
unnamed: R4.1, U1.4
unnamed: D1.4, R4.2
OLED_C1N: C8.2, J2.4
OLED_C1P: C8.1, J2.3
OLED_C2N: C9.2, J2.2
OLED_C2P: C9.1, J2.1
OLED_IREF: J2.12, R6.1
OLED_RES: C7.1, J2.9, R5.2
OLED_VCOMH: C10.1, J2.13
OLED_VOUT: C11.1, J2.14

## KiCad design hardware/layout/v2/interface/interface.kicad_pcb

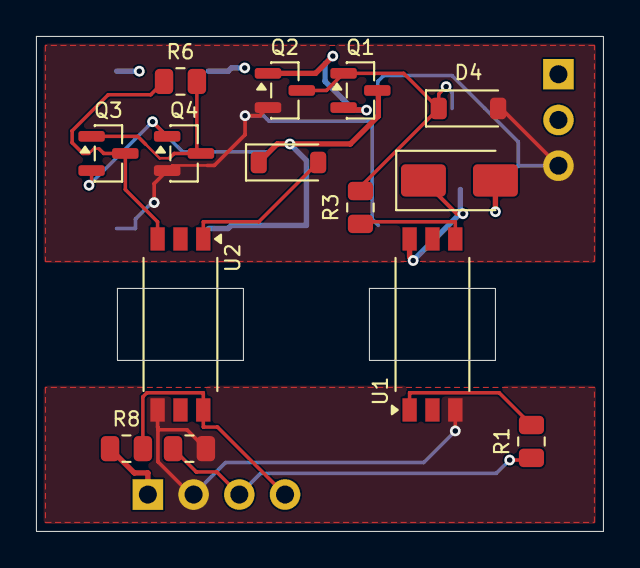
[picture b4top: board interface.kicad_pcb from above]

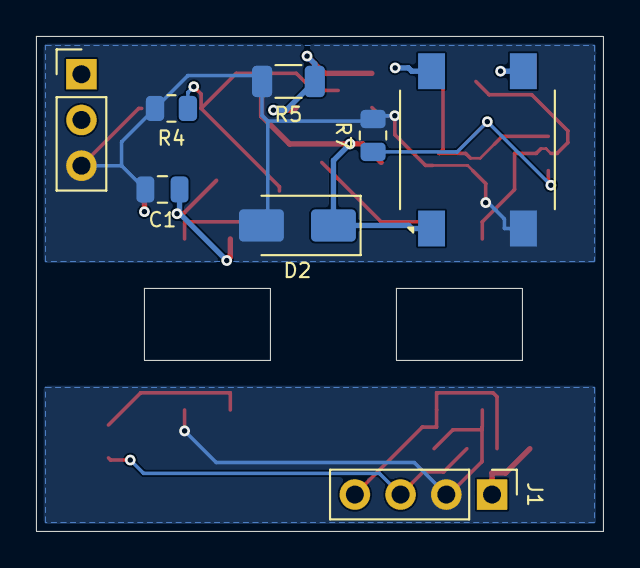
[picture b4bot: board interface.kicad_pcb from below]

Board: 4 copper layers, 31.5 x 27.5 mm, 22 parts (8 on the bottom side), 17 nets.

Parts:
C1: 1u 50V; C_0805_2012Metric
D1: DF06S; Diode_Bridge_Vishay_DFS
D2: SMAJ24A; D_SMA
D3: SS16; D_SMA
D4: 12V; D_SOD-123
D5: 5V6; D_SOD-123
J1: Main logic; PinHeader_1x04_P2.54mm_Vertical
J2: Main DALI; PinHeader_1x03_P2.54mm_Vertical
Q1: IRLML0060; SOT-23
Q2, Q3, Q4: BC847; SOT-23
R1: 330R; R_0805_2012Metric
R2, R4: 10k; R_0805_2012Metric
R3, R8: 4k7; R_0805_2012Metric
R5: 2R; R_1206_3216Metric
R6: 100k; R_0805_2012Metric
R7: 680R; R_0805_2012Metric
U1, U2: TLP383(D4BLLTL,E; SO-6L_10x3.84mm_P1.27mm

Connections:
+3V3: J1.1, R8.1
DA1: D1.3, J2.1
DA2: D1.4, J2.2
DALI_BOOT: C1.1, D3.1, U1.6
DALI_GATE: D4.1, Q1.1, Q2.3, R3.2, R4.1
DALI_GATE_SW: R3.1, U1.4
DALI_RX: J1.4, R8.2, U2.6
DALI_SENSE: Q1.2, Q2.1, R5.1
DALI_TX: J1.3, R1.1, R2.1
DA_P: D1.1, D2.1, D3.2, D5.1, Q1.3
GND: J1.2, R2.2, U1.3, U2.4
GNDD: C1.2, D1.2, D2.2, D4.2, J2.3, Q2.2, Q4.2, R4.2, R5.2, R7.2
unnamed: R1.2, U1.1
unnamed: D5.2, U2.1
unnamed: Q3.2, Q4.1, R7.1
unnamed: Q3.1, Q4.3, R6.2
RX_LIM_IN: Q3.3, R6.1, U2.3

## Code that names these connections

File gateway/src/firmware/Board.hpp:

#pragma once

#include <cstddef>
#include <cstdint>

#include <driver/gpio.h>
#include <hal/adc_types.h>
#include <hal/uart_types.h>

// Unified XIAO ESP32-C6 pin map across V2 (2 DIN) and V3 (1 DIN):
//   D0  / GPIO0  = LED_DATA         (SK6805-EC15 RGB chain: index 0 D1 STATUS, 1 D2 KNX, 2 D3 DALI)
//   D1  / GPIO1  = DALI_SUPPLY_OFF  (high switches the isolated REC3-2415SRW/H2/A/CTRL DALI supply off)
//   D2  / GPIO2  = BTN_LADDER       (ADC1_CH2: 10k pull-up to 3V3, SW1 SCROLL 10k, SW2 RESET 20k)
//   D3  / GPIO21 = NC               (unconnected spare GPIO)
//   D4  / GPIO22 = I2C_SDA          (SSD1306 OLED on UI board, I2C address 0x3C)
//   D5  / GPIO23 = I2C_SCL          (SSD1306 OLED on UI board)
//   D6  / GPIO16 = KNX_RXD          (MCU UART1 TX -> 1k series R -> NCN5130 SDI/RXD pin 27)
//   D7  / GPIO17 = KNX_TXD          (NCN5130 SDO/TXD pin 28 -> MCU UART1 RX)
//   D8  / GPIO19 = DALI_RX          (RX optocoupler collector; bus high = logic low)
//   D9  / GPIO20 = NCN_SAVEB        (NCN5130 SAVEB open-drain power-warning input, active low)
//   D10 / GPIO18 = DALI_TX          (TX optocoupler LED; high = bus low)
namespace gateway::firmware::board {

constexpr gpio_num_t led_data = GPIO_NUM_0;         // XIAO D0
constexpr std::size_t led_count = 3;                // D1 STATUS (0), D2 KNX (1), D3 DALI (2)
constexpr gpio_num_t dali_supply_off = GPIO_NUM_1;  // XIAO D1 (active high = supply off)
constexpr gpio_num_t button_ladder = GPIO_NUM_2;    // XIAO D2 (ADC1_CH2)
constexpr adc_unit_t button_adc_unit = ADC_UNIT_1;
constexpr adc_channel_t button_adc_channel = ADC_CHANNEL_2;
constexpr gpio_num_t i2c_sda = GPIO_NUM_22;  // XIAO D4
constexpr gpio_num_t i2c_scl = GPIO_NUM_23;  // XIAO D5
constexpr uart_port_t knx_uart = UART_NUM_1;
constexpr gpio_num_t knx_tx = GPIO_NUM_16;  // XIAO D6 -> NCN5130 SDI/RXD
constexpr gpio_num_t knx_rx = GPIO_NUM_17;  // XIAO D7 <- NCN5130 SDO/TXD
constexpr std::uint32_t knx_baud = 19200;
constexpr gpio_num_t dali_rx = GPIO_NUM_19;    // XIAO D8
constexpr gpio_num_t ncn_saveb = GPIO_NUM_20;  // XIAO D9
constexpr gpio_num_t dali_tx = GPIO_NUM_18;    // XIAO D10
// On the gateway PCB, DALI_TX high turns the TX optocoupler on (pulling the bus
// low), and bus idle high turns the RX optocoupler on (pulling DALI_RX low).
constexpr bool dali_invert_tx = false;
constexpr bool dali_invert_rx = true;

constexpr bool usb_pin(gpio_num_t pin) {
    return pin == GPIO_NUM_12 || pin == GPIO_NUM_13;
}

constexpr bool pins_distinct() {
    const gpio_num_t pins[] = {
        led_data, dali_supply_off, button_ladder, i2c_sda,   i2c_scl,
        knx_tx,   knx_rx,          dali_rx,       ncn_saveb, dali_tx,
    };
    for (std::size_t i = 0; i < sizeof(pins) / sizeof(pins[0]); ++i) {
        if (usb_pin(pins[i])) {
            return false;
        }
        for (std::size_t j = i + 1; j < sizeof(pins) / sizeof(pins[0]); ++j) {
            if (pins[i] == pins[j]) {
                return false;
            }
        }
    }
    return true;
}

static_assert(pins_distinct(), "board pins must be distinct and must not use USB D-/D+ (GPIO12/13)");

}

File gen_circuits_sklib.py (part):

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            Pin(num='6',name='VBUS1',func=pin_types.PWRIN,unit=1),
            Pin(num='2',name='VBUS2',func=pin_types.PWRIN,unit=1),
            Pin(num='3',name='TX0',func=pin_types.OUTPUT,unit=1),
            Pin(num='4',name='CCP',func=pin_types.PASSIVE,unit=1),
            Pin(num='5',name='CAV',func=pin_types.PASSIVE,unit=1),
            Pin(num='7',name='CEQ1',func=pin_types.PASSIVE,unit=1),
            Pin(num='8',name='CEQ2',func=pin_types.PASSIVE,unit=1),
            Pin(num='9',name='VFILT',func=pin_types.PWROUT,unit=1),
            Pin(num='10',name='V20V',func=pin_types.PWROUT,unit=1),
            Pin(num='1',name='VSSA',func=pin_types.PWRIN,unit=1),
            Pin(num='16',name='VIN',func=pin_types.PWRIN,unit=1),
            Pin(num='17',name='VSW1',func=pin_types.OUTPUT,unit=1),
            Pin(num='18',name='VSS1',func=pin_types.PWRIN,unit=1),
            Pin(num='19',name='VDD1',func=pin_types.PWROUT,unit=1),
            Pin(num='20',name='VDD1M',func=pin_types.INPUT,unit=1),
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            Pin(num='31',name='VSSD',func=pin_types.PWRIN,unit=1),
            Pin(num='32',name='XCLK',func=pin_types.OUTPUT,unit=1),
            Pin(num='33',name='XSEL',func=pin_types.INPUT,unit=1),
            Pin(num='34',name='XTAL2',func=pin_types.BIDIR,unit=1),
            Pin(num='35',name='XTAL1',func=pin_types.INPUT,unit=1),
            Pin(num='36',name='SAVEB',func=pin_types.OPENCOLL,unit=1),
            Pin(num='37',name='RESETB',func=pin_types.OPENCOLL,unit=1),
            Pin(num='38',name='FANIN',func=pin_types.INPUT,unit=1),
            Pin(num='39',name='ANAOUT',func=pin_types.OUTPUT,unit=1),
            Pin(num='40',name='VDDA',func=pin_types.PWRIN,unit=1)], 'unit_defs':[] }),
        Part(**{ 'name':'R', 'dest':TEMPLATE, 'tool':SKIDL, 'aliases':Alias({'R'}), 'ref_prefix':'R', 'fplist':[''], 'footprint':'Resistor_SMD:R_0603_1608Metric', 'keywords':'R res resistor', 'description':'Resistor', 'datasheet':'', 'pins':[
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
